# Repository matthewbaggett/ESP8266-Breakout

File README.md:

# ESP8266 Breakout

Originally just a ESP8266 broken out onto a 22pin DIP header, has become an ESP8266 on a 24pin DIP header with built in 3.3v regulator ([AMS1117](http://www.aliexpress.com/premium/ams1117.html?ltype=wholesale&SearchText=ams1117&d=y&origin=y&initiative_id=SB_20151010010621&isViewCP=y&catId=0)), and built-in USB programmer ([CH340G](http://www.aliexpress.com/item/Free-shipping-50pcs-lot-CH340G-CH340-SOP16-IC-Best-quality/32420752742.html?spm=2114.13010208.99999999.261.F5FuUg)) and all the associated recommended pullups as per the [Arduino ESP8266 project](https://github.com/esp8266/Arduino) ([Schematic](https://github.com/esp8266/Arduino/blob/esp8266/docs/ESP_improved_stability.png)

# Licence

<br />This work is licensed under a <a rel="license" href="http://creativecommons.org/licenses/by-nc/4.0/">Creative Commons Attribution-NonCommercial 4.0 International License</a>.

May be re-licenced on request.

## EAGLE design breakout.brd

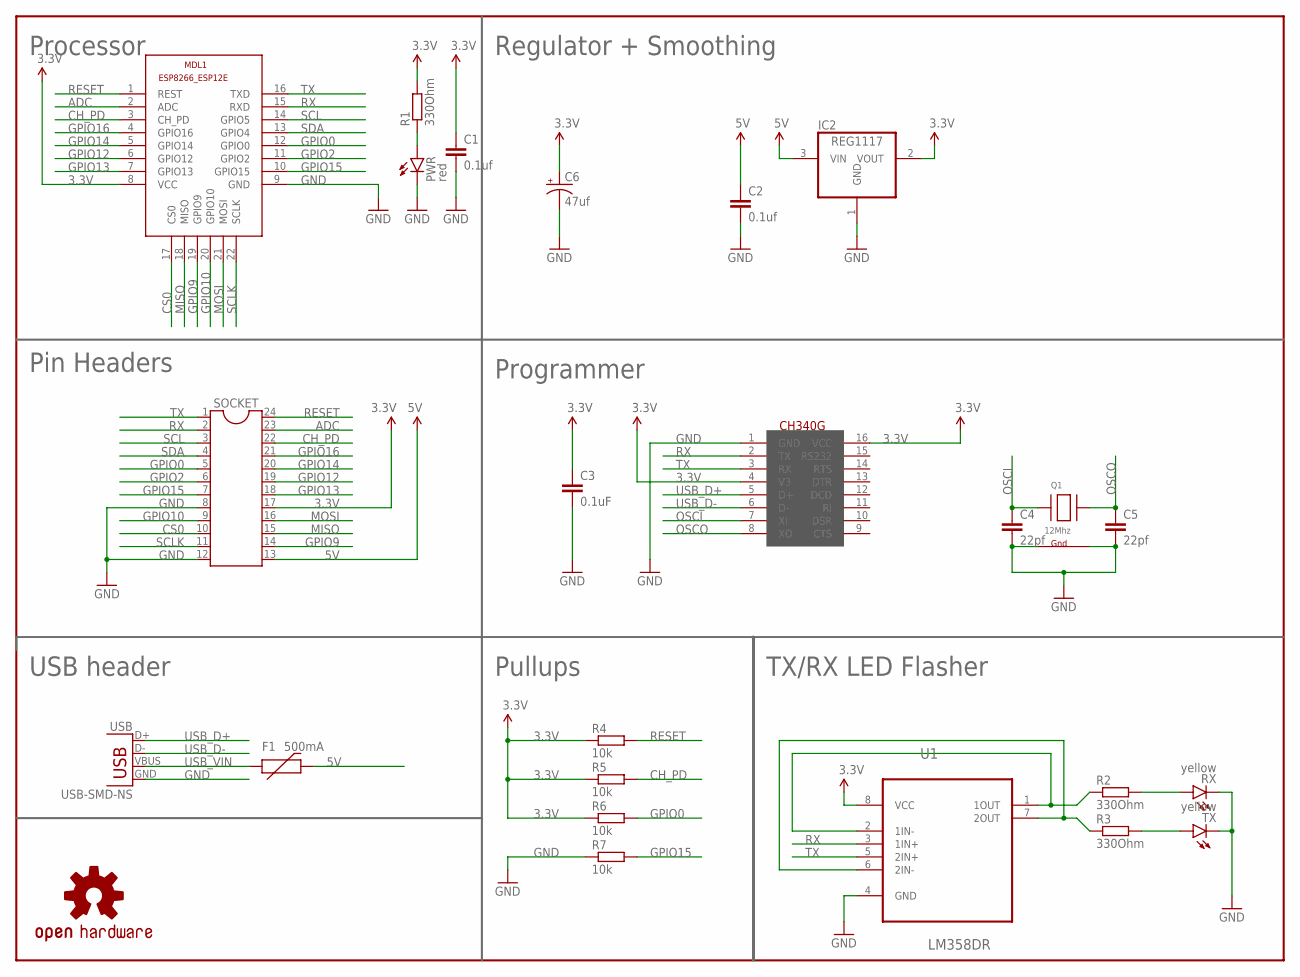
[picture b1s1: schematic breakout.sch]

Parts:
C1, C2: 0.1uf; C0805
C3: 0.1uF; C0805
C4, C5: 22pf; C0805
C6: 47uf; PANASONIC_C
F1: 500mA; PTC-1206
FRAME1: FRAME-LETTERNO_PACKAGE; DUMMY
IC2: REG1117; SOT223
LOGO1: OSHW-LOGOS; OSHW-LOGO-S
MDL1: ESP8266-12EESP8266-ESP12E; ESP8266-ESP12E
PWR: red; LED-0603
Q1: 12Mhz; NX3225
R1, R2, R3: 330Ohm; R0805
R4, R5, R6, R7: 10k; R0805
RX: yellow; LED-0603
SOCKET: DIL24-9
TX: yellow; LED-0603
U1: LM358DR; SOIC127P600X175-8N
U$1: CH340G; SOIC16
USB: USB-SMD-NS; USB-MINIB-NOSTOP

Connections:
3.3V: C1.1, C3.1, C6.+, IC2.2 (VOUT), MDL1.8 (VCC), R1.2, R4.1, R5.1, R6.1, SOCKET.17, U1.8 (VCC), U$1.4 (V3), U$1.16 (VCC)
5V: C2.1, F1.2, IC2.3 (VIN), SOCKET.13
ADC: MDL1.2 (ADC), SOCKET.23
CH_PD: MDL1.3 (CH_PD), R5.2, SOCKET.22
CS0: MDL1.17 (CS0), SOCKET.10
GND: C1.2, C2.2, C3.2, C4.2, C5.2, C6.-, IC2.1 (GND), MDL1.9 (GND), PWR.C, Q1.2 (G2), Q1.4 (G1), R7.1, RX.C, SOCKET.8, SOCKET.12, TX.C, U1.4 (GND), U$1.1 (GND), USB.GND
GPIO0: MDL1.12 (GPIO0), R6.2, SOCKET.5
GPIO2: MDL1.11 (GPIO2), SOCKET.6
GPIO9: MDL1.19 (GPIO9), SOCKET.14
GPIO10: MDL1.20 (GPIO10), SOCKET.9
GPIO12: MDL1.6 (GPIO12), SOCKET.19
GPIO13: MDL1.7 (GPIO13), SOCKET.18
GPIO14: MDL1.5 (GPIO14), SOCKET.20
GPIO15: MDL1.10 (GPIO15), R7.2, SOCKET.7
GPIO16: MDL1.4 (GPIO16), SOCKET.21
MISO: MDL1.18 (MISO), SOCKET.15
MOSI: MDL1.21 (MOSI), SOCKET.16
unnamed: PWR.A, R1.1
unnamed: R3.2, TX.A
unnamed: R2.1, U1.1 (1OUT), U1.2 (1IN-)
unnamed: R3.1, U1.6 (2IN-), U1.7 (2OUT)
unnamed: R2.2, RX.A
OSCI: C4.1, Q1.1 (X1), U$1.7 (XI)
OSCO: C5.1, Q1.3 (X2), U$1.8 (XO)
RESET: MDL1.1 (REST), R4.2, SOCKET.24
RX: MDL1.15 (RXD), SOCKET.2, U1.3 (1IN+), U$1.2 (TX)
SCL: MDL1.14 (GPIO5), SOCKET.3
SCLK: MDL1.22 (SCLK), SOCKET.11
SDA: MDL1.13 (GPIO4), SOCKET.4
TX: MDL1.16 (TXD), SOCKET.1, U1.5 (2IN+), U$1.3 (RX)
USB_D+: U$1.5 (D+), USB.D+
USB_D-: U$1.6 (D-), USB.D-
USB_VIN: F1.1, USB.VBUS

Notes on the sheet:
Programmer
Regulator + Smoothing
Processor
Pin Headers
USB header
Pullups
TX/RX LED Flasher

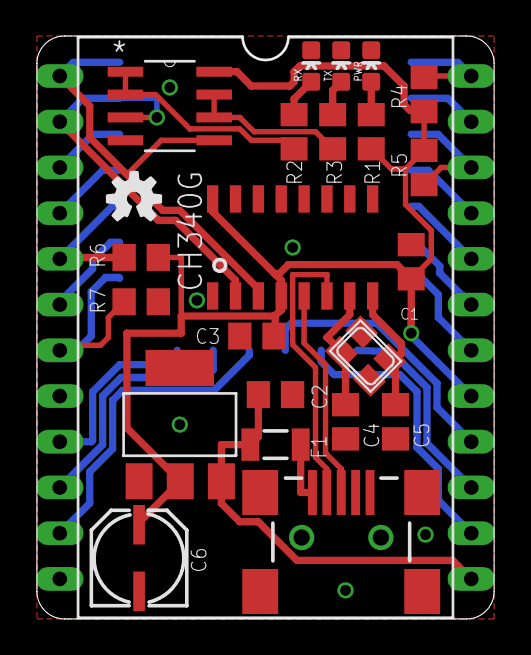
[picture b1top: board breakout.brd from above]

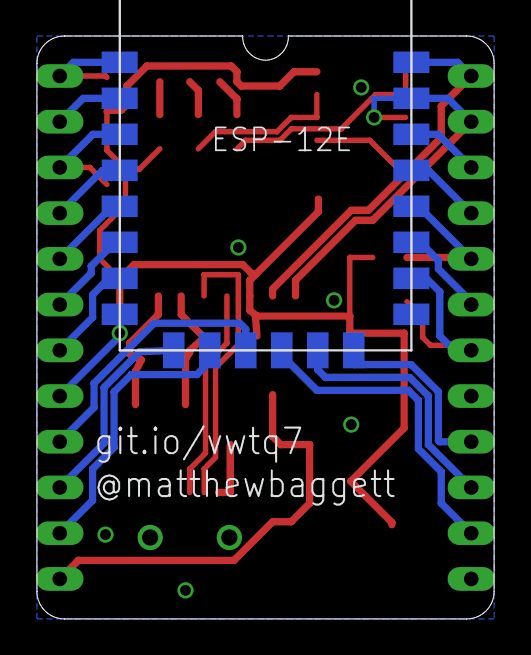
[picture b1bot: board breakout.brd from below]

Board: 2 copper layers, 25.4 x 32.4 mm, 26 parts (2 on the bottom side), 33 nets.

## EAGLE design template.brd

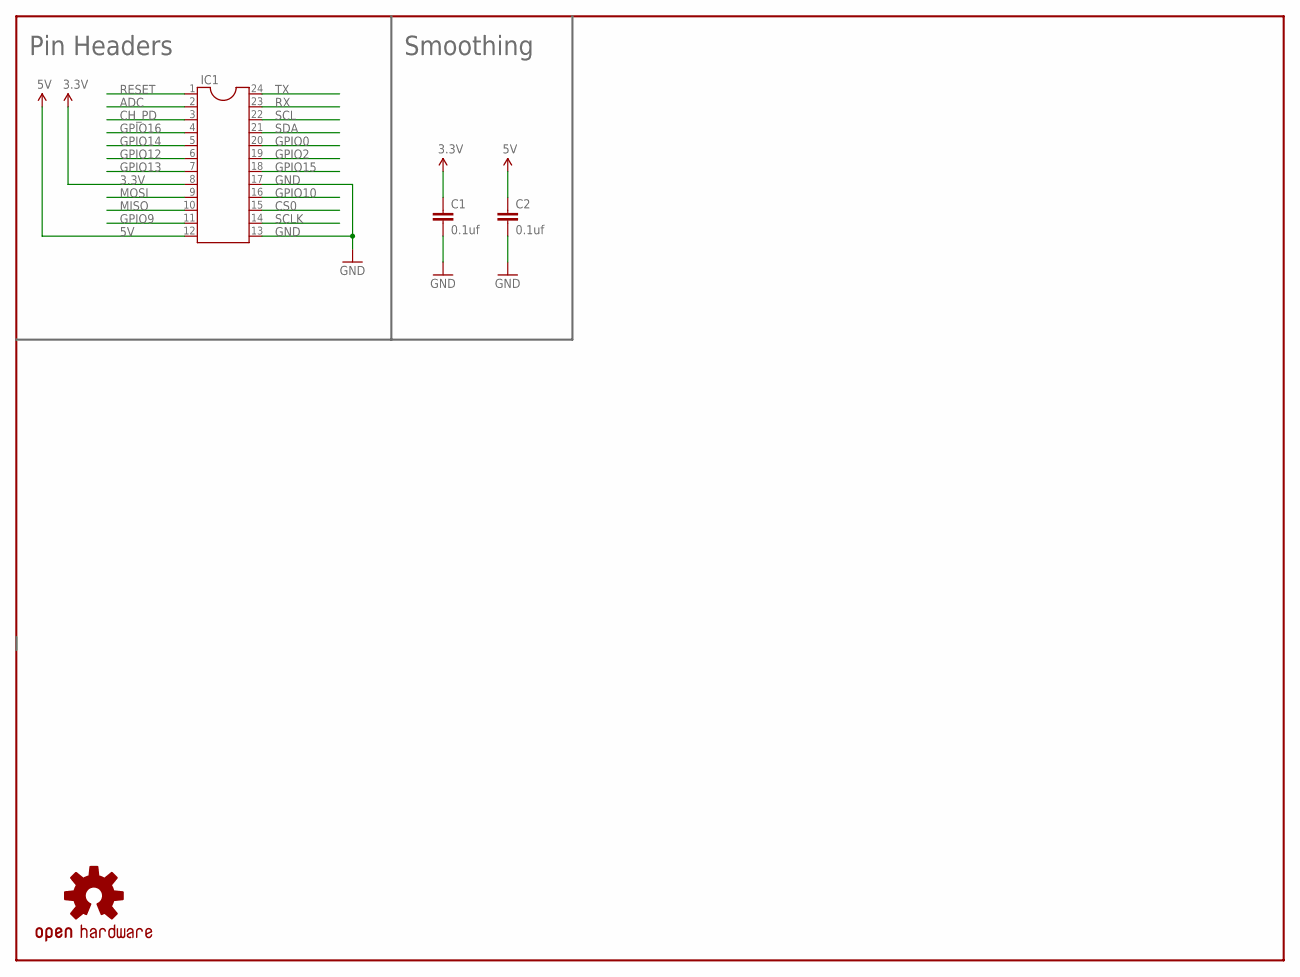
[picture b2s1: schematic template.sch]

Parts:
C1, C2: 0.1uf; 1206
FRAME1: FRAME-LETTERNO_PACKAGE; DUMMY
IC1: DIL24-9
LOGO1: OSHW-LOGOS; OSHW-LOGO-S

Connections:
3.3V: C1.1, IC1.8
5V: C2.1, IC1.12
ADC: IC1.2
CH_PD: IC1.3
CS0: IC1.15
GND: C1.2, C2.2, IC1.13, IC1.17
GPIO0: IC1.20
GPIO2: IC1.19
GPIO9: IC1.11
GPIO10: IC1.16
GPIO12: IC1.6
GPIO13: IC1.7
GPIO14: IC1.5
GPIO15: IC1.18
GPIO16: IC1.4
MISO: IC1.10
MOSI: IC1.9
RESET: IC1.1
RX: IC1.23
SCL: IC1.22
SCLK: IC1.14
SDA: IC1.21
TX: IC1.24

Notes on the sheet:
Pin Headers
Smoothing

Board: 2 copper layers, 5 parts (1 on the bottom side), 3 nets, no tracks yet.

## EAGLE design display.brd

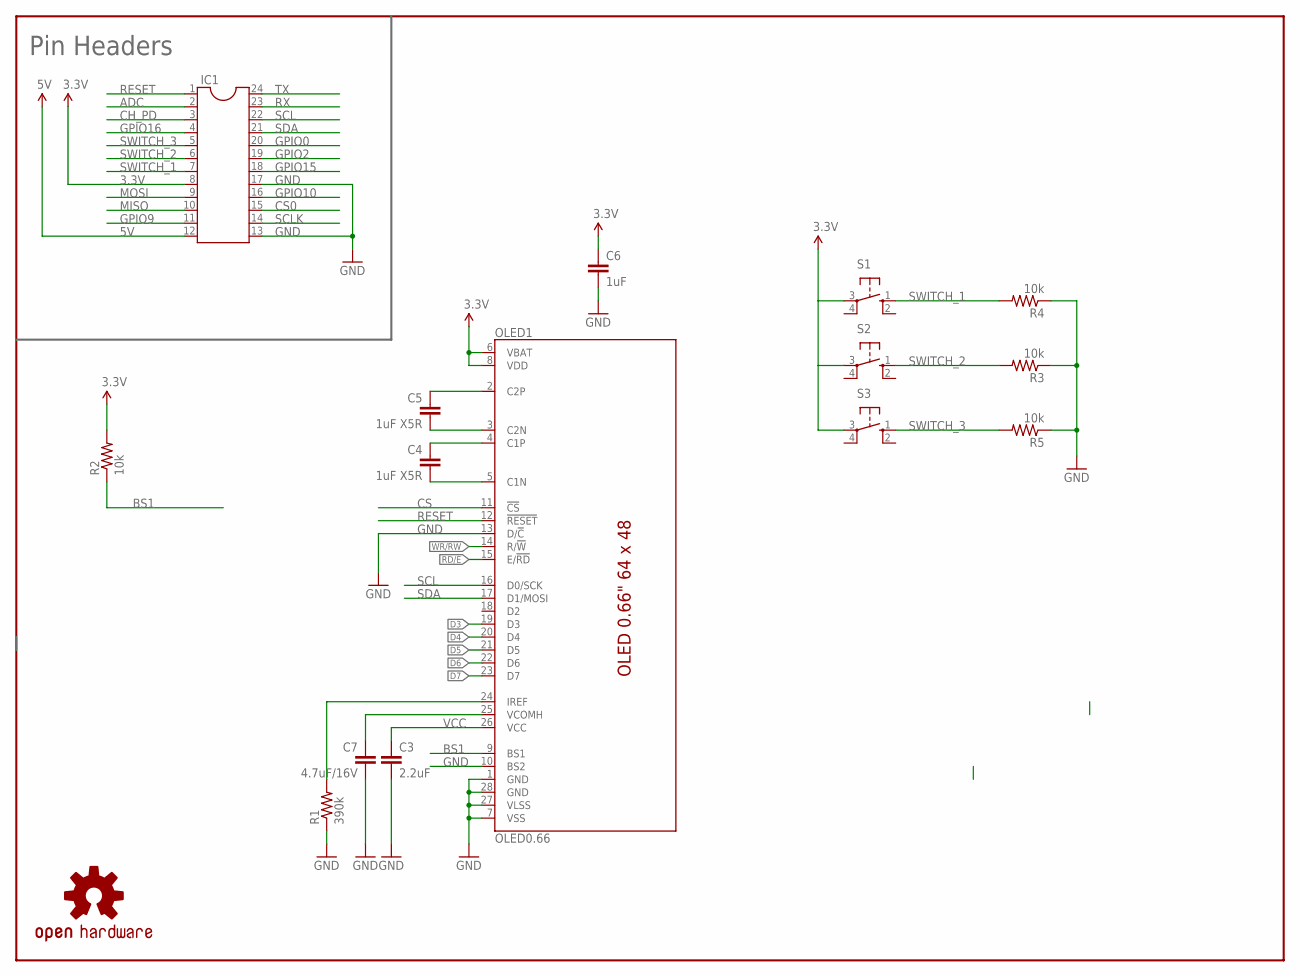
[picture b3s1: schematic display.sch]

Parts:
C3: 2.2uF; 1206
C4, C5: 1uF X5R; 1206
C6: 1uF; 1206
C7: 4.7uF/16V; 1206
FRAME1: FRAME-LETTERNO_PACKAGE; DUMMY
IC1: DIL24-9
LOGO1: OSHW-LOGOS; OSHW-LOGO-S
OLED1: OLED0.66; OLED-0.66-64X48
R1: 390k; 1206
R2, R3, R4, R5: 10k; 1206
S1, S2, S3: 10-XX; B3F-10XX

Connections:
3.3V: C6.1, IC1.8, OLED1.6 (VBAT), OLED1.8 (VDD), R2.2, S1.3, S2.3, S3.3
5V: IC1.12
ADC: IC1.2
BS1: OLED1.9 (BS1), R2.1
C1N: C4.2, OLED1.5 (C1N)
C1P: C4.1, OLED1.4 (C1P)
C2N: C5.2, OLED1.3 (C2N)
C2P: C5.1, OLED1.2 (C2P)
CH_PD: IC1.3
CS: OLED1.11 (!CS!)
CS0: IC1.15
D3: OLED1.19 (D3)
D4: OLED1.20 (D4)
D5: OLED1.21 (D5)
D6: OLED1.22 (D6)
D7: OLED1.23 (D7)
GND: C3.2, C6.2, C7.2, IC1.13, IC1.17, OLED1.1 (GND), OLED1.7 (VSS), OLED1.10 (BS2), OLED1.13 (D/!C!), OLED1.27 (VLSS), OLED1.28 (GND), R1.1, R3.1, R4.1, R5.1
GPIO0: IC1.20
GPIO2: IC1.19
GPIO9: IC1.11
GPIO10: IC1.16
GPIO15: IC1.18
GPIO16: IC1.4
IREF: OLED1.24 (IREF), R1.2
MISO: IC1.10
MOSI: IC1.9
RD/E: OLED1.15 (E/!RD!)
RESET: IC1.1, OLED1.12 (!RESET!)
RX: IC1.23
SCL: IC1.22, OLED1.16 (D0/SCK)
SCLK: IC1.14
SDA: IC1.21, OLED1.17 (D1/MOSI)
SWITCH_1: IC1.7, R4.2, S1.1 (S)
SWITCH_2: IC1.6, R3.2, S2.1 (S)
SWITCH_3: IC1.5, R5.2, S3.1 (S)
TX: IC1.24
VCC: C3.1, OLED1.26 (VCC)
VCOMH: C7.1, OLED1.25 (VCOMH)
WR/RW: OLED1.14 (R/!W!)

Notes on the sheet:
Pin Headers

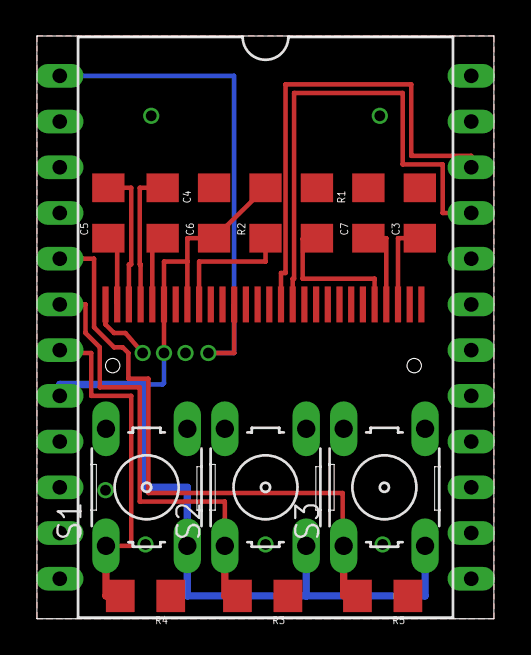
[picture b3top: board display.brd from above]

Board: 2 copper layers, 25.4 x 32.4 mm, 17 parts (1 on the bottom side), 16 nets.

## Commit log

2015-10-09 Tidy up for publishing
2015-10-10 Added FTDI + USB support on the board. Also cleaned up the schematic. DRC pass.
2015-10-10 Slight revision to the GND plane.
2015-10-10 Set licence.
2015-10-30 Adding a blank sheild
2015-10-30 Adding a cute little OLED display based upon https://www.sparkfun.com/products/13003
2015-10-30 Revision to switch around TX/RX lines so that this thing actually works, detach RTS signal from RESET, add TX & RX LEDs + assoc. resistors. Renamed GPIO4 & GPIO5 as SDA and SCL respectively to suit t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
2015-10-30 Renamed GPIO4 & GPIO5 as SDA and SCL respectively to suit their default i2c states.
2015-10-31 Stencil holder for DirtyPCBs stencils.
2015-10-31 Bigger knockouts to assist in removing stencil.
2015-12-23 CH340G
2015-12-23 fix ignores
2015-12-23 Fix a DRC error..
2016-01-31 Updated images of the board and schematic to reflect the use of a CH340G instead of FTDI's FT232RL due to cost
2016-02-01 Added a polarised 47uf size B capacitor to the 3.3v rail. Removed thermals from fill layers
2016-04-16 Fuck it, 0805 all the things, smaller crystal, rejig everything to solder in a less PITA way.
2016-04-16 Added TX/RX LEDs. Aww yiss.
2016-04-16 update path
2016-04-16 FT232RL is dirty awfulness from FTDI. Stuff their business practices.
2016-04-17 Add labels
2016-04-17 adding some dimentions
2016-04-18 Missing line for the LM358DR
2016-04-18 remove some labels
2016-04-18 updated graphic
2016-04-18 Rounded corners + notch.
2016-04-18 Faffing with ground

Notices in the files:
parts and their libraries:
SparkFun-LED: Licensing: Creative Commons ShareAlike 4.0 International - https://creativecommons.org/licenses/by-sa/4.0
SparkFun-Aesthetics: Released under the Creative Commons Attribution Share-Alike 4.0 License
SparkFun-Aesthetics: https://creativecommons.org/licenses/by-sa/4.0
